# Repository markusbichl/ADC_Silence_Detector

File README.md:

# ADC Silence Detector

A compact embedded device that monitors analog audio input and automatically cuts power to a downstream USB ADC when silence is detected - eliminating idle noise and unnecessary power draw.

---

## Overview

The ADC Silence Detector sits inline between your audio source and your USB ADC. It continuously monitors the analog audio signal on both left and right channels. As long as audio is present, the USB-A output port stays powered. Once silence is sustained, the device cuts USB power to the connected ADC, effectively turning it off without any manual intervention.

When audio resumes, power is restored and the downstream ADC comes back on automatically.

---

## Hardware

### Connectors

| Port | Type | Function |
|------|------|----------|
| Power In | Mini-USB | 5 V power supply input |
| Audio In/Out L | RCA (double) | Left channel analog passthrough |
| Audio In/Out R | RCA (double) | Right channel analog passthrough |
| Power Out | USB-A | Switched 5 V output for the controlled ADC |

### Signal Path

```
Audio Source ──► RCA In (L+R) ──► passthrough ──► RCA Out (L+R) ──► Downstream equipment
                      │
                      └──► ADC Level sensing (PA6 / PB0)
                                      │
                                      ▼
                              CH32X033 MCU
                                      │
                                      ▼
Mini-USB In ──────────────────► USB-A Out (switched via PB1)
```

The audio signal path is fully passive - the RCA inputs are wired straight through to the RCA outputs with no active components in the signal chain, preserving audio quality.

---

## Firmware

### Microcontroller

**WCH CH32X033** - 32-bit RISC-V (rv32imacxw) running at 48 MHz from the internal HSI oscillator.

- IDE: MounRiver Studio 2

### Detection Logic

The firmware polls both ADC channels every 500 ms and takes the higher of the two readings as the current audio level. A hysteresis comparator prevents rapid toggling around the threshold:

| Condition | 12-bit ADC value | Action |
|-----------|-----------------|--------|
| Output OFF, level rises above | 20 | Turn USB-A output **ON** |
| Output ON, level falls below | 10 | Turn USB-A output **OFF** |

**ADC channels:**

| Pin | ADC Channel | Signal |
|-----|-------------|--------|
| PA6 | CH6 | Left channel level |
| PB0 | CH8 | Right channel level |

**Output pin:** PB1 drives the USB-A power switch.

### Source Layout

```
SW
  User/
    main.c                      - application logic (ADC poll loop, hysteresis, GPIO control)
    system_ch32x035.c           - clock initialisation
    ch32x035_it.c               - interrupt handlers (unused stubs)
  Core/
    core_riscv.c/h              - RISC-V core support
  Debug/
    debug.c/h                   - SDI printf (debug UART over single wire)
  Peripheral/
    src/  inc/                  - WCH standard peripheral library
  Startup/
    startup_ch32x035.S          - reset vector and startup code
  Ld/
    Link.ld                     - linker script
PCB/
  ADC_Silence_detecor.kicad_pcb - KiCAD PCB
  ADC_Silence_detecor.kicad_sch - KiCAD Schematic
  jlcpcb/                       - Gerber files
CAD/
  case.stl                      - STL file of a simple Case
  ADC_Silence_detector.step     - STEP file of the populated PCB
  ADC_Silence_detector.stl      - STL file of the populated PCB
Demo
  ADC_Silence_detector.jpg      - Photo of the finished build
  PCB_populated.png             - Rendering of the populated PCB
```

---

## Building & Flashing

1. Open the project in **MounRiver Studio 2**.
2. Select the `obj` build configuration and click **Build** (or press `Ctrl+B`).
3. Connect a WCH-Link programmer to the SWD/SDI header.
4. Click **Download** to flash the `.hex` to the CH32X033.

Debug output is available over SDI (single-wire debug interface) at 115200 baud and prints the raw ADC level on every poll cycle.

---

## License

Peripheral library files are copyright Nanjing Qinheng Microelectronics Co., Ltd. Application code is released under the same terms - see individual file headers for details.

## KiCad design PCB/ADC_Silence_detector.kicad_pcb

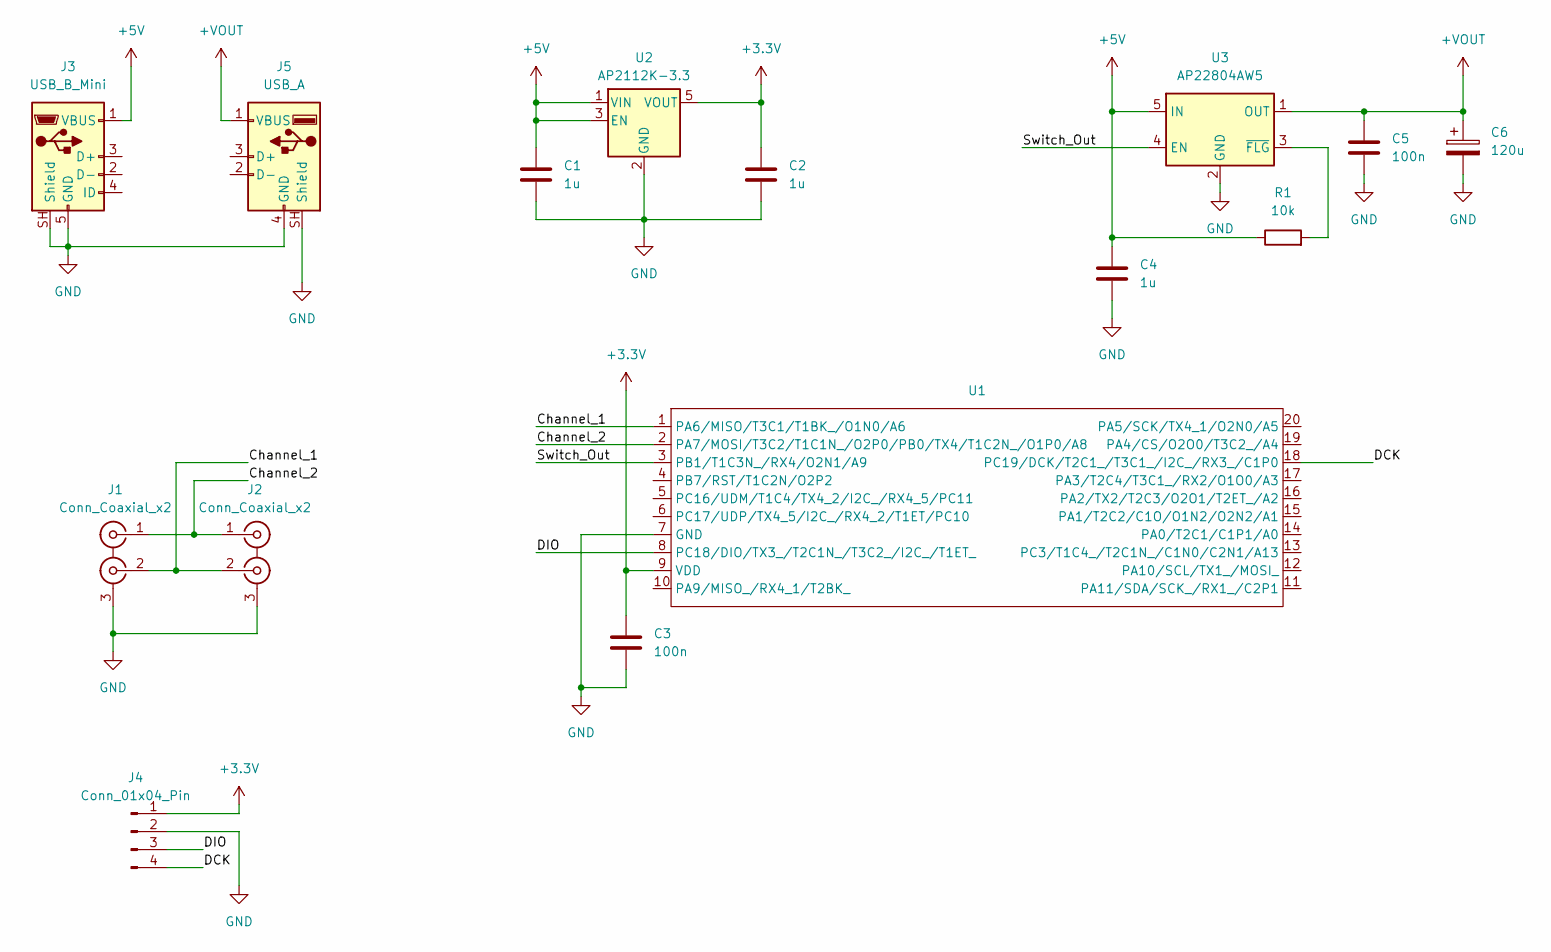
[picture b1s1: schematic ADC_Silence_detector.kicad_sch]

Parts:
C1, C2, C4: 1u; C_1206_3216Metric_Pad1.33x1.80mm_HandSolder
C3, C5: 100n; C_1206_3216Metric_Pad1.33x1.80mm_HandSolder
C6: 120u; CP_Elec_6.3x5.8
J1, J2: Conn_Coaxial_x2; BNC_Win_364A2x95_Horizontal
J3: USB_B_Mini; USB_Mini-B_Wuerth_65100516121_Horizontal
J4: Conn_01x04_Pin; PinHeader_1x04_P2.54mm_Vertical
J5: USB_A; USB_A_Connfly_DS1095
R1: 10k; R_1206_3216Metric_Pad1.30x1.75mm_HandSolder
U1: TSSOP-20_L6.5-W4.4-P0.65-LS6.4-BL; Manufacturer Part CH32X033F8P6; LCSC Part Name CH32X033F8P6
U2: AP2112K-3.3; SOT-23-5_HandSoldering
U3: AP22804AW5; SOT-23-5

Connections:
+3.3V: C2.1, C3.1, J4.1, U1.9 (VDD), U2.5 (VOUT)
+5V: C1.1, C4.1, J3.1 (VBUS), R1.1, U2.1 (VIN), U2.3 (EN), U3.5 (IN)
+VOUT: C5.1, C6.1, J5.1 (VBUS), U3.1 (OUT)
/Channel_1: J1.2 (IN2), J2.2 (IN2), U1.1 (PA6/MISO/T3C1/T1BK_/O1N0/A6)
/Channel_2: J1.1 (IN1), J2.1 (IN1), U1.2 (PA7/MOSI/T3C2/T1C1N_/O2P0/PB0/TX4/T1C2N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)
/DCK: J4.4, U1.18 (PC19/DCK/T2C1_/T3C1_/I2C_/RX3_/C1P0)
/DIO: J4.3, U1.8 (PC18/DIO/TX3_/T2C1N_/T3C2_/I2C_/T1ET_)
/Switch_Out: U1.3 (PB1/T1C3N_/RX4/O2N1/A9), U3.4 (EN)
GND: C1.2, C2.2, C3.2, C4.2, C5.2, C6.2, J1.3 (EXT), J2.3 (EXT), J3.5 (GND), J3.SH (Shield), J4.2, J5.4 (GND), J5.SH (Shield), U1.7 (GND), U2.2 (GND), U3.2 (GND)
unnamed: R1.2, U3.3 (~FLG)

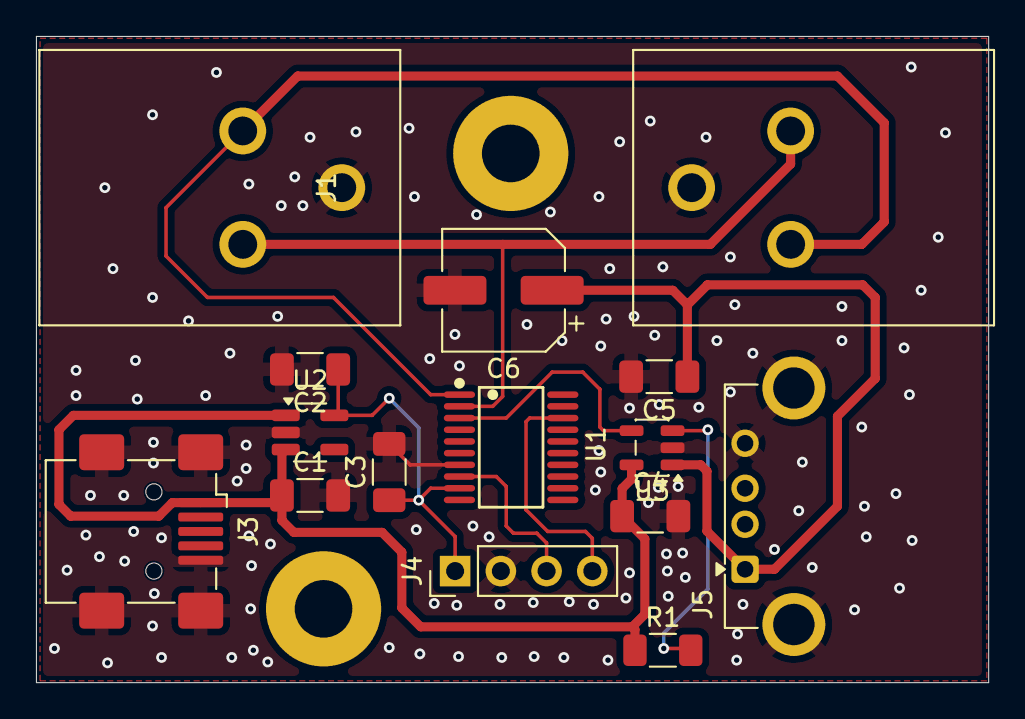
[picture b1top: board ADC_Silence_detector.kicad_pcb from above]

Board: 2 copper layers, 52.9 x 35.9 mm, 17 parts (0 on the bottom side), 10 nets.

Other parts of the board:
MH1, MH2: MountingHole_3.2mm_M3_Pad

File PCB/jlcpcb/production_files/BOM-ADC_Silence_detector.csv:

Comment,Designator,Footprint,LCSC,Quantity
100n,C3,C_1206_3216Metric_Pad1.33x1.80mm_HandSolder,,1
1u,C2,C_1206_3216Metric_Pad1.33x1.80mm_HandSolder,,1
Conn_01x04_Pin,J4,PinHeader_1x04_P2.54mm_Vertical,,1
USB_A,J5,USB_A_Connfly_DS1095,,1
USB_B_Mini,J3,USB_Mini-B_Wuerth_65100516121_Horizontal,,1
10k,R1,R_1206_3216Metric_Pad1.30x1.75mm_HandSolder,,1
~,U1,TSSOP-20_L6.5-W4.4-P0.65-LS6.4-BL,,1
1u,C1,C_1206_3216Metric_Pad1.33x1.80mm_HandSolder,,1
AP2112K-3.3,U2,SOT-23-5_HandSoldering,,1
Conn_Coaxial_x2,J2,BNC_Win_364A2x95_Horizontal,,1
Conn_Coaxial_x2,J1,BNC_Win_364A2x95_Horizontal,,1
AP22804AW5,U3,SOT-23-5,,1
120u,C6,CP_Elec_6.3x5.8,,1
100n,C5,C_1206_3216Metric_Pad1.33x1.80mm_HandSolder,,1
1u,C4,C_1206_3216Metric_Pad1.33x1.80mm_HandSolder,,1

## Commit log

2026-05-28 Fixed hysteresis, added timeouts, added pause detection
2026-05-28 Added README, new project structure
2026-05-28 Move leftovers to new structure, updated gitignore
2026-05-28 Added PCB, CAD and Demo
